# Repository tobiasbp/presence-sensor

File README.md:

# presence-sensor
A presence sensor PCB for rhythm games or art projects

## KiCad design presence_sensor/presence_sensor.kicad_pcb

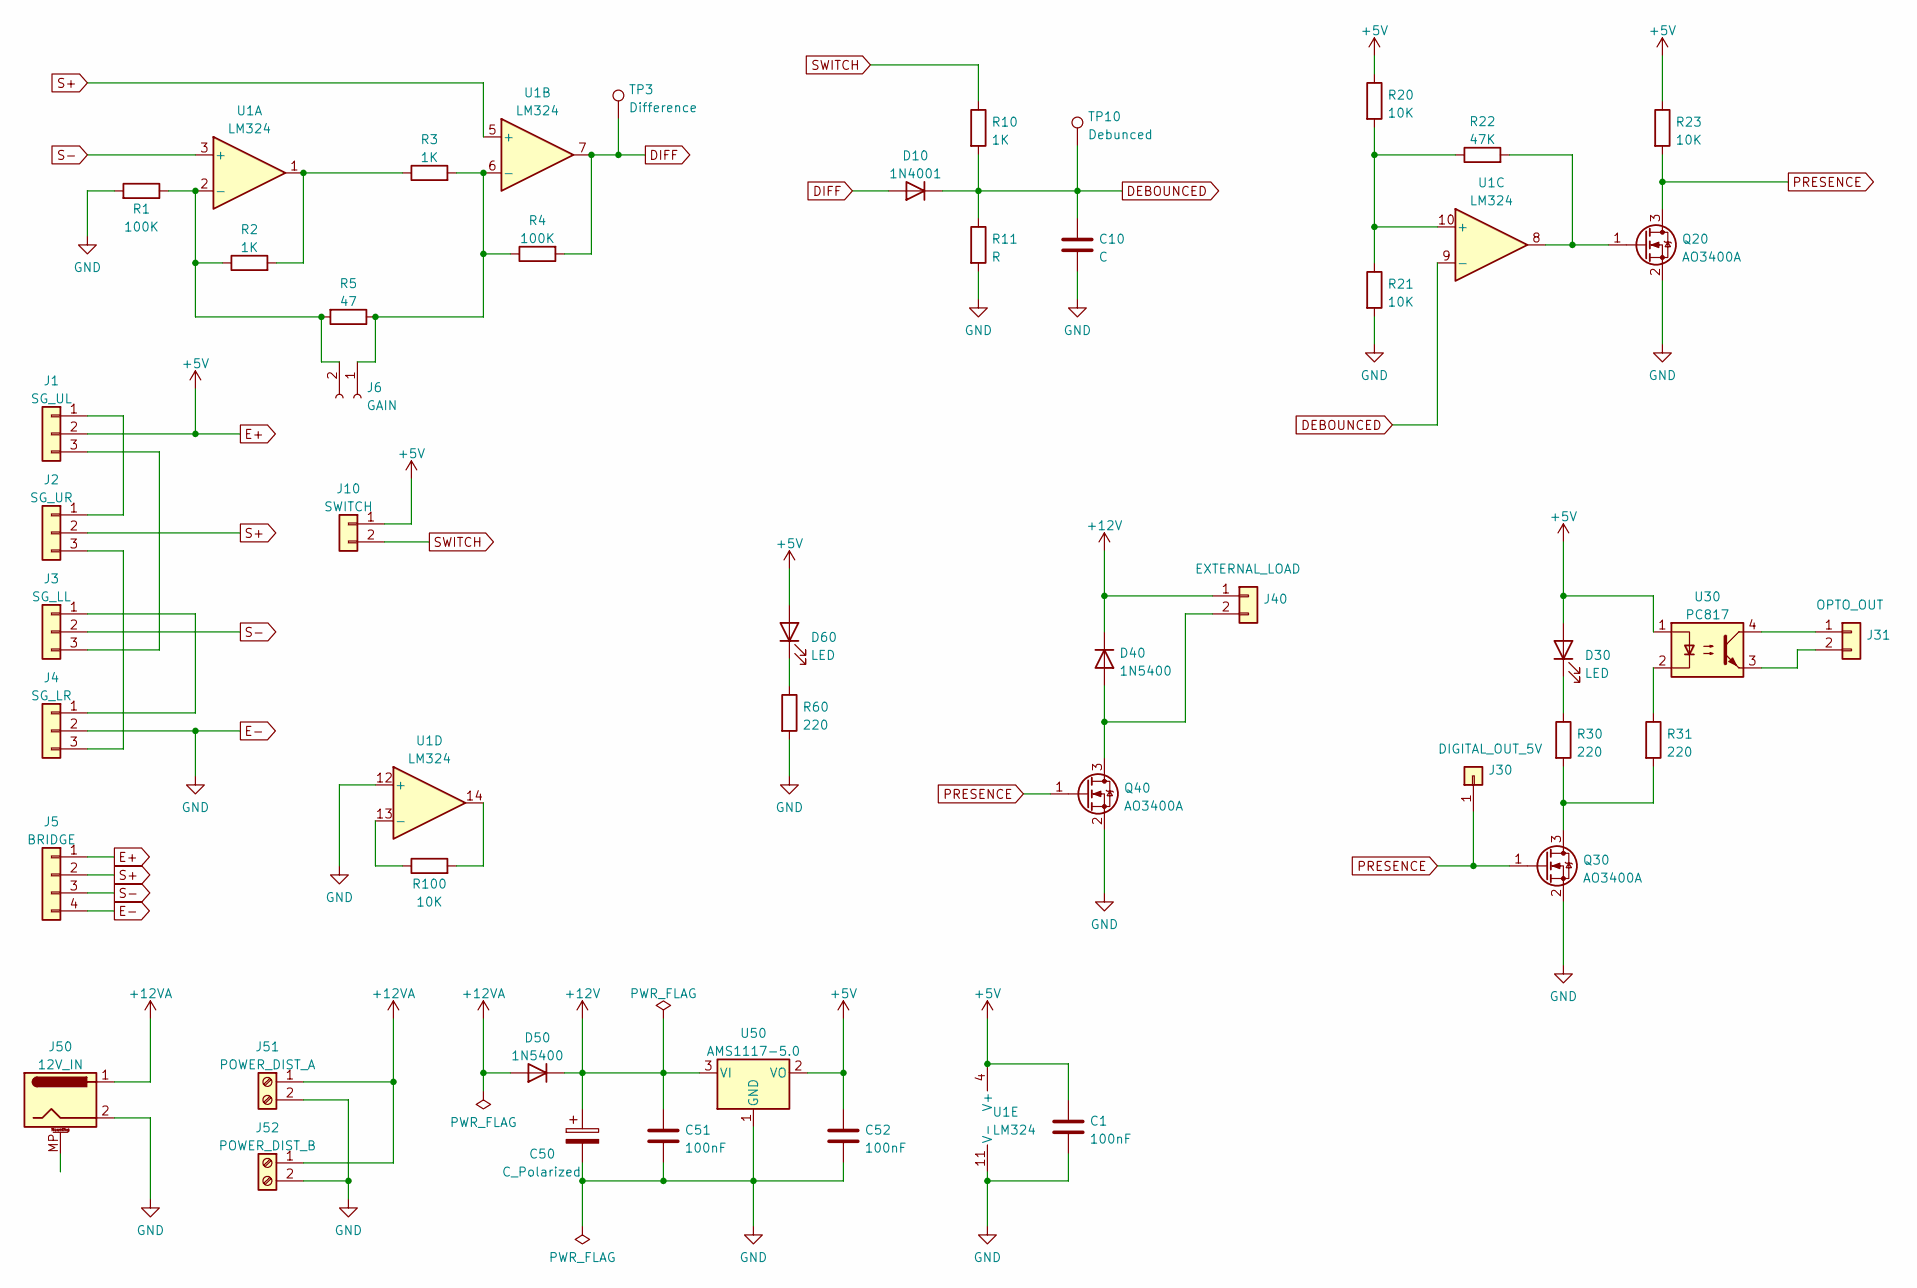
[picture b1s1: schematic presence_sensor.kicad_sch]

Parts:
C1, C51, C52: 100nF; C_1206_3216Metric_Pad1.33x1.80mm_HandSolder
C10: C; C_1206_3216Metric_Pad1.33x1.80mm_HandSolder
C50: C_Polarized; CP_Radial_D8.0mm_P5.00mm
D10: 1N4001; D_1206_3216Metric_Pad1.42x1.75mm_HandSolder
D30, D60: LED; LED_1206_3216Metric_Pad1.42x1.75mm_HandSolder
D40, D50: 1N5400; D_DO-35_SOD27_P10.16mm_Horizontal
J1: SG_UL; PinHeader_1x03_P2.54mm_Vertical
J2: SG_UR; PinHeader_1x03_P2.54mm_Vertical
J3: SG_LL; PinHeader_1x03_P2.54mm_Vertical
J4: SG_LR; PinHeader_1x03_P2.54mm_Vertical
J5: BRIDGE; PinHeader_1x04_P2.54mm_Vertical
J6: GAIN; PinHeader_1x02_P2.54mm_Vertical
J10: SWITCH; PinHeader_1x02_P2.54mm_Vertical
J30: DIGITAL_OUT_5V; PinHeader_1x01_P2.54mm_Vertical
J31: OPTO_OUT; PinHeader_1x02_P2.54mm_Vertical
J40: EXTERNAL_LOAD; PinHeader_1x02_P2.54mm_Vertical
J50: 12V_IN; BarrelJack_Horizontal
J51: POWER_DIST_A; TerminalBlock_bornier-2_P5.08mm
J52: POWER_DIST_B; TerminalBlock_bornier-2_P5.08mm
Q20, Q30, Q40: AO3400A; SOT-23
R1, R4: 100K; R_1206_3216Metric_Pad1.30x1.75mm_HandSolder
R2, R3, R10: 1K; R_1206_3216Metric_Pad1.30x1.75mm_HandSolder
R5: 47; R_1206_3216Metric_Pad1.30x1.75mm_HandSolder
R11: R; R_1206_3216Metric_Pad1.30x1.75mm_HandSolder
R20, R21, R23, R100: 10K; R_1206_3216Metric_Pad1.30x1.75mm_HandSolder
R22: 47K; R_1206_3216Metric_Pad1.30x1.75mm_HandSolder
R30, R31, R60: 220; R_1206_3216Metric_Pad1.30x1.75mm_HandSolder
TP3: Difference; TestPoint_Pad_D1.0mm
TP10: Debunced; TestPoint_Pad_D1.0mm
U1: LM324; SOIC-14_3.9x8.7mm_P1.27mm
U30: PC817; DIP-4_W7.62mm
U50: AMS1117-5.0; SOT-223-3_TabPin2

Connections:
+12V: C50.1, C51.1, D40.1 (K), D50.1 (K), J40.1, U50.3 (VI)
+12VA: D50.2 (A), J50.1, J51.1, J52.1
DEBOUNCED: C10.1, D10.1 (K), R10.2, R11.1, TP10.1, U1.9 (-)
DIFF: D10.2 (A), R4.2, TP3.1, U1.7
E+: C1.1, C52.1, D30.2 (A), D60.2 (A), J1.2, J5.1, J10.1, R20.1, R23.1, U1.4 (V+), U30.1, U50.2 (VO)
E-: C1.2, C10.2, C50.2, C51.2, C52.2, J4.2, J5.4, J50.2, J51.2, J52.2, Q20.2 (S), Q30.2 (S), Q40.2 (S), R1.2, R11.2, R21.2, R60.2, U1.11 (V-), U1.12 (+), U50.1 (GND)
unnamed: D30.1 (K), R30.1
unnamed: D40.2 (A), J40.2, Q40.3 (D)
unnamed: D60.1 (K), R60.1
unnamed: J1.1, J2.1
unnamed: J1.3, J3.3
unnamed: J2.3, J4.3
unnamed: J3.1, J4.1
unnamed: J6.1, R3.2, R4.1, R5.1, U1.6 (-)
unnamed: J6.2, R1.1, R2.1, R5.2, U1.2 (-)
unnamed: J31.1, U30.4
unnamed: J31.2, U30.3
unnamed: Q20.1 (G), R22.2, U1.8
unnamed: Q30.3 (D), R30.2, R31.2
unnamed: R2.2, R3.1, U1.1
unnamed: R20.2, R21.1, R22.1, U1.10 (+)
unnamed: R31.1, U30.2
unnamed: R100.1, U1.13 (-)
unnamed: R100.2, U1.14
PRESENCE: J30.1, Q20.3 (D), Q30.1 (G), Q40.1 (G), R23.2
S+: J2.2, J5.2, U1.5 (+)
S-: J3.2, J5.3, U1.3 (+)
SWITCH: J10.2, R10.1

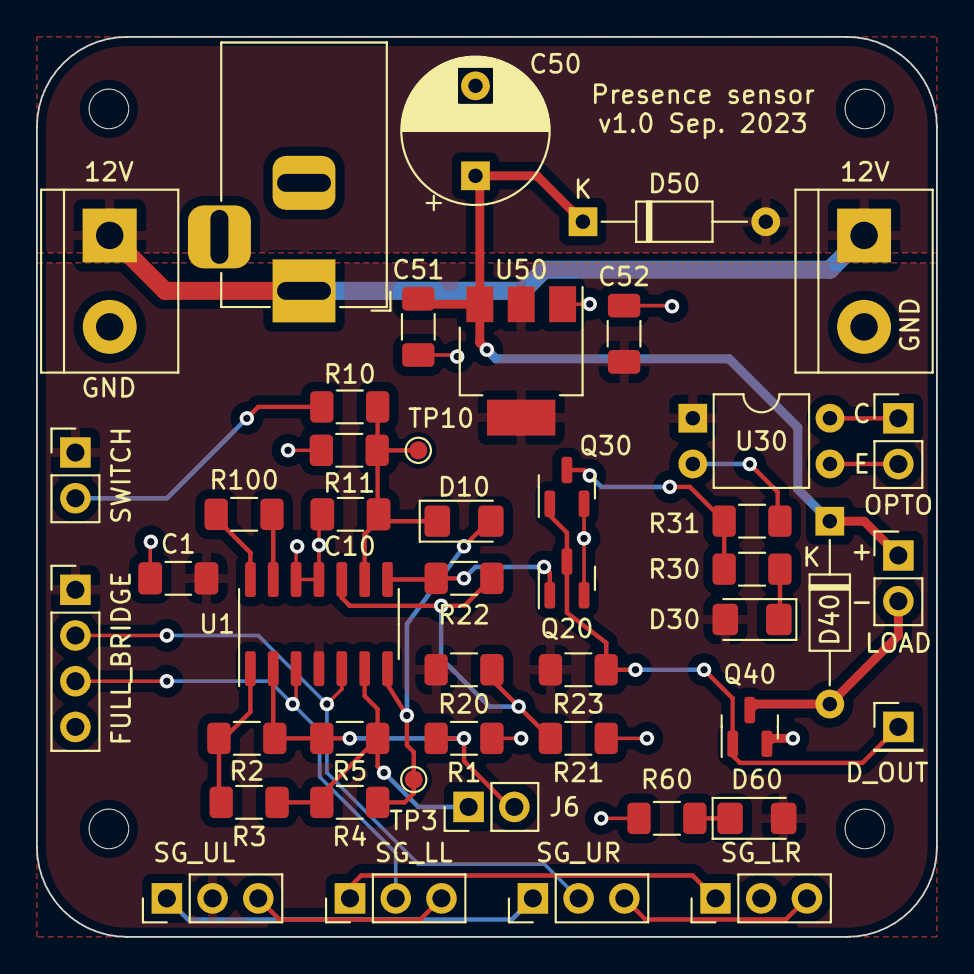
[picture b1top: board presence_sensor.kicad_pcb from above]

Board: 2 copper layers, 50.0 x 50.0 mm, 46 parts (0 on the bottom side), 28 nets.

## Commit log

2023-09-25 Initial commit pf PCB v1.0
2023-09-26 Remove unneeded testpoints
2023-09-26 Minor rerouting for beauty
2023-09-26 Add labels on silkscreen for outputs. Minor rerouting for beauty.
2023-09-26 Move power indicator LED.
2023-09-26 Move presence indicator LED.
2023-09-26 Add mounting holes
2023-09-26 Added v1.0 Gerbers
